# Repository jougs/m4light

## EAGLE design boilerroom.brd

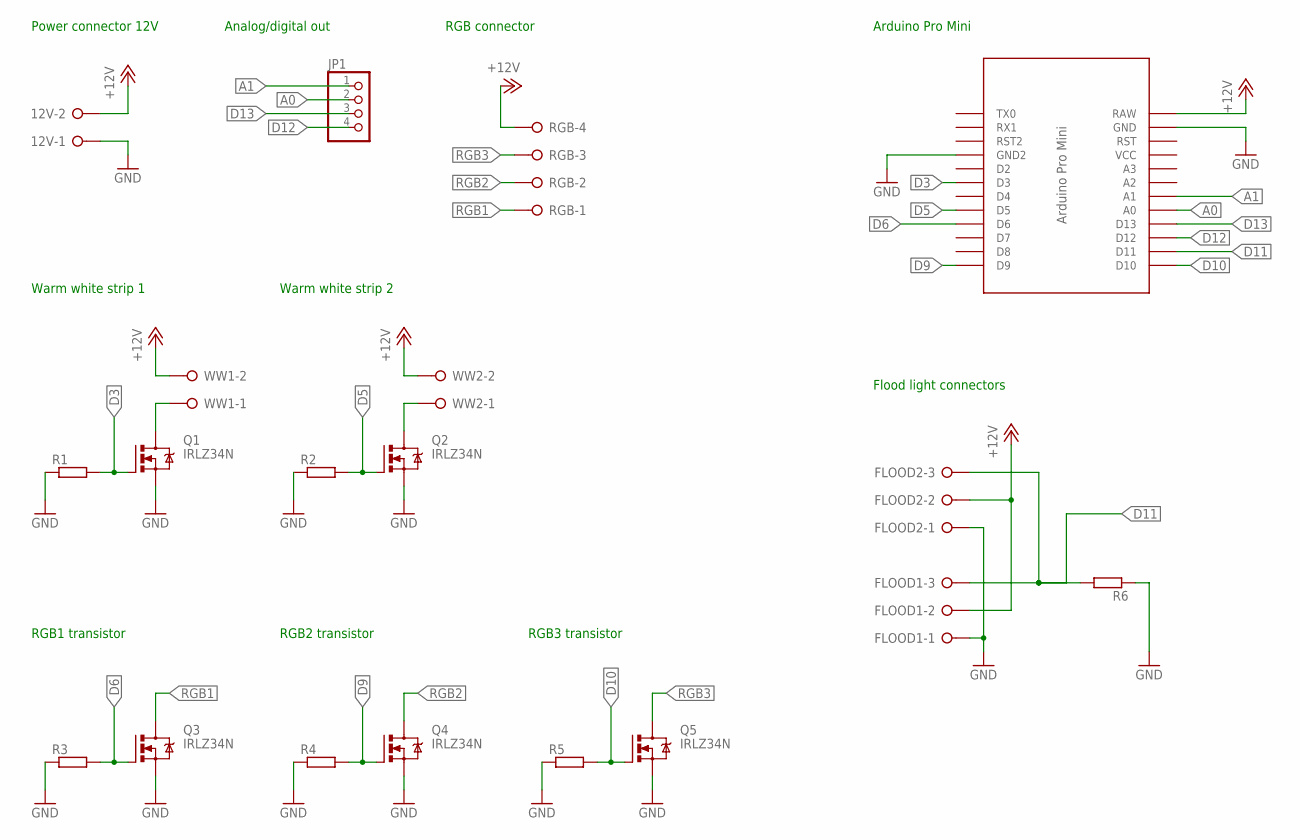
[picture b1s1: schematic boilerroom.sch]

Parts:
12V: W237-02P; W237-132
FLOOD1, FLOOD2: W237-03P; W237-133
JP1: PINHD-1X4; 1X04
Q1, Q2, Q3, Q4, Q5: IRLZ34N; TO220BV
R1, R2, R3, R4, R5, R6: R-EU_0207/10; 0207/10
RGB: W237-04P; W237-4P
U$2: PRO-MINI-3V3
WW1, WW2: W237-02P; W237-132

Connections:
+12V: 12V.2, FLOOD1.2, FLOOD2.2, RGB.4, U$2.RAW, WW1.2, WW2.2
A0: JP1.2, U$2.A0
A1: JP1.1, U$2.A1
D3: Q1.G, R1.2, U$2.D3
D5: Q2.G, R2.2, U$2.D5
D6: Q3.G, R3.2, U$2.D6
D9: Q4.G, R4.2, U$2.D9
D10: Q5.G, R5.2, U$2.D10
D11: FLOOD1.3, FLOOD2.3, R6.2, U$2.D11
D12: JP1.4, U$2.D12
D13: JP1.3, U$2.D13
GND: 12V.1, FLOOD1.1, FLOOD2.1, Q1.S, Q2.S, Q3.S, Q4.S, Q5.S, R1.1, R2.1, R3.1, R4.1, R5.1, R6.1, U$2.GND, U$2.GND1 (GND2)
unnamed: Q2.D, WW2.1
RGB1: Q3.D, RGB.1
RGB2: Q4.D, RGB.2
RGB3: Q5.D, RGB.3
WW1-: Q1.D, WW1.1

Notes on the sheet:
Flood light connectors
Warm white strip 1
Warm white strip 2
Power connector 12V
RGB connector
Analog/digital out
Arduino Pro Mini
RGB1 transistor
RGB2 transistor
RGB3 transistor

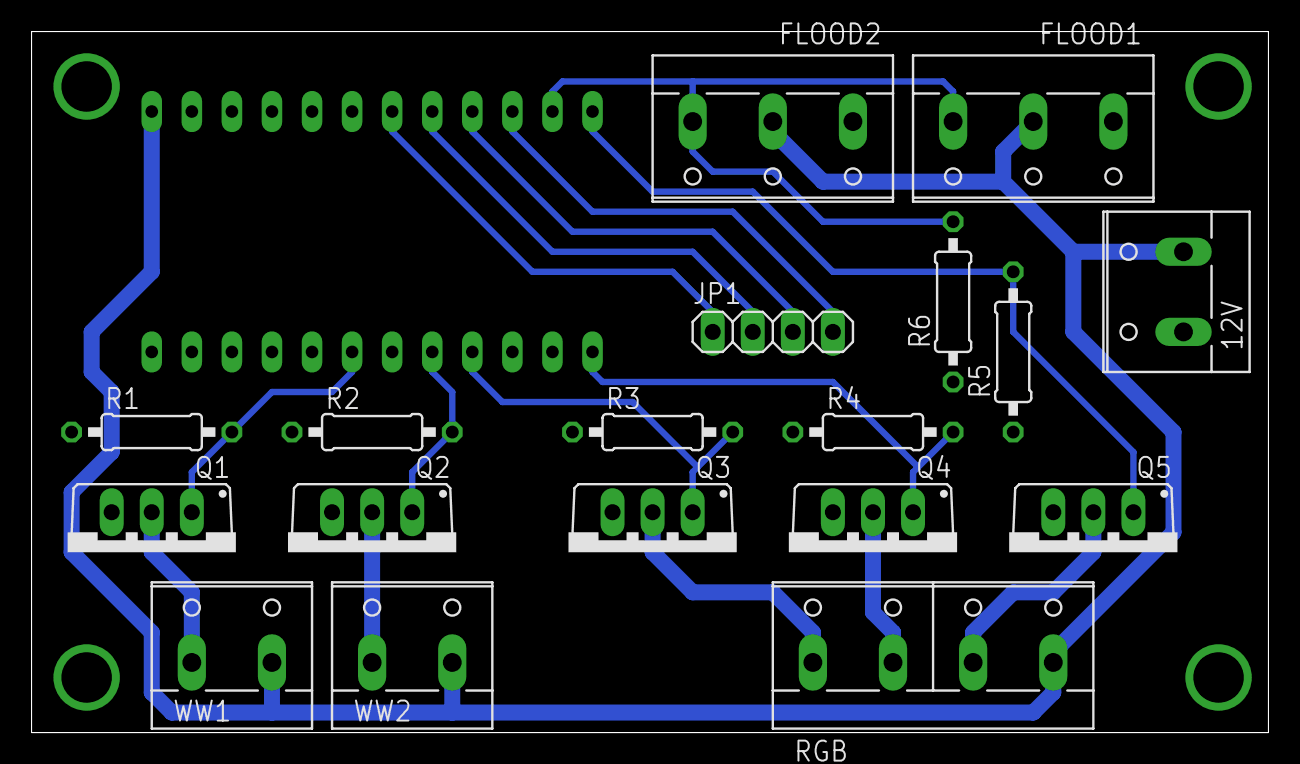
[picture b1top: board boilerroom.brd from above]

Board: 2 copper layers, 78.4 x 44.4 mm, 19 parts (0 on the bottom side), 17 nets.

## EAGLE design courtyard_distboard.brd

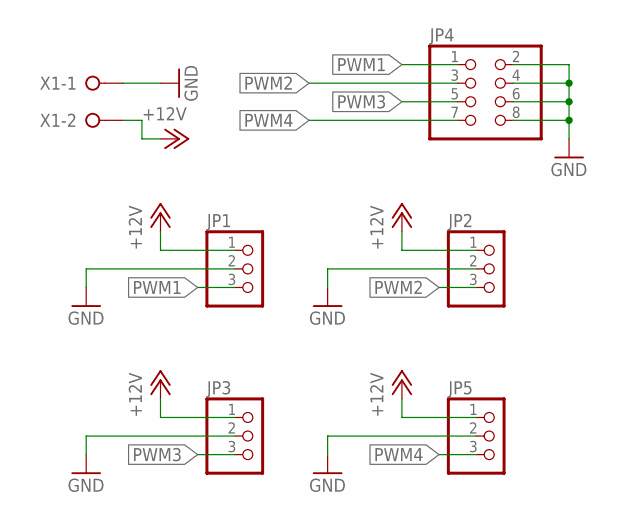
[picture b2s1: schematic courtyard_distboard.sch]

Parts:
JP1, JP2, JP3, JP5: PINHD-1X3; 1X03
JP4: PINHD-2X4; 2X04
X1: W237-02P; W237-132

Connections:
+12V: JP1.1, JP2.1, JP3.1, JP5.1, X1.2
GND: JP1.2, JP2.2, JP3.2, JP4.2, JP4.4, JP4.6, JP4.8, JP5.2, X1.1
PWM1: JP1.3, JP4.1
PWM2: JP2.3, JP4.3
PWM3: JP3.3, JP4.5
PWM4: JP4.7, JP5.3

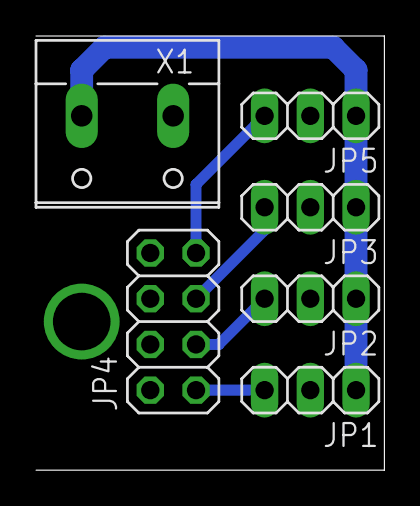
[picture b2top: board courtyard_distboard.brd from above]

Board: 2 copper layers, 19.4 x 24.1 mm, 6 parts (0 on the bottom side), 6 nets.

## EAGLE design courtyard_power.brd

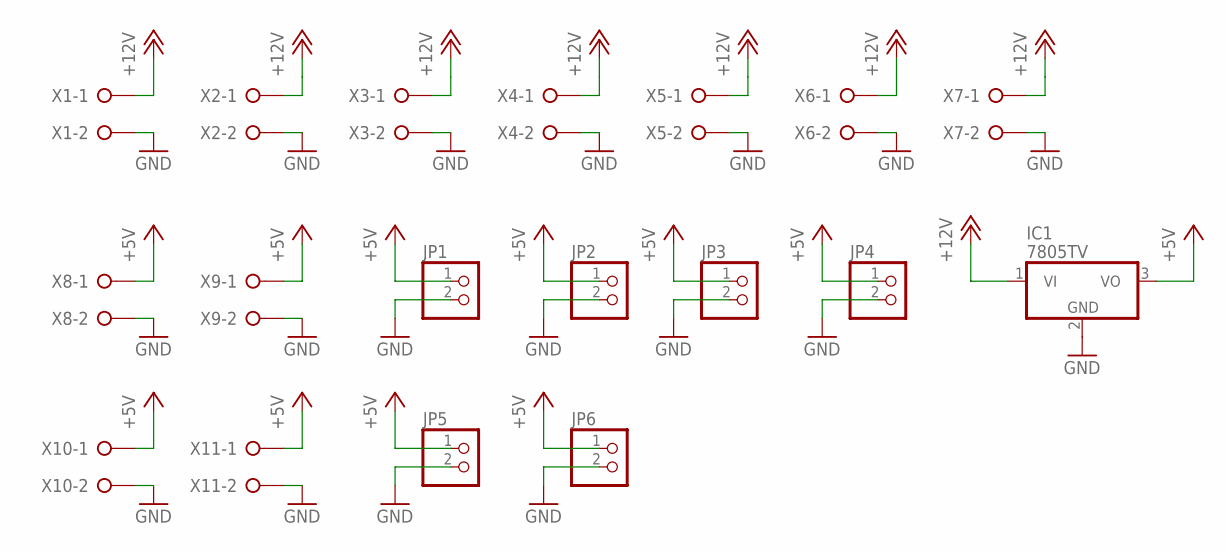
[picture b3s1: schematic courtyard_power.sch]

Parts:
IC1: 7805TV; TO220V
JP1, JP2, JP3, JP4, JP5, JP6: PINHD-1X2; 1X02
X1, X2, X3, X4, X5, X6, X7, X8, X9, X10, X11: W237-02P; W237-132

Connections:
+5V: IC1.3 (VO), JP1.1, JP2.1, JP3.1, JP4.1, JP5.1, JP6.1, X8.1, X9.1, X10.1, X11.1
+12V: IC1.1 (VI), X1.1, X2.1, X3.1, X4.1, X5.1, X6.1, X7.1
GND: IC1.2 (GND), JP1.2, JP2.2, JP3.2, JP4.2, JP5.2, JP6.2, X1.2, X2.2, X3.2, X4.2, X5.2, X6.2, X7.2, X8.2, X9.2, X10.2, X11.2

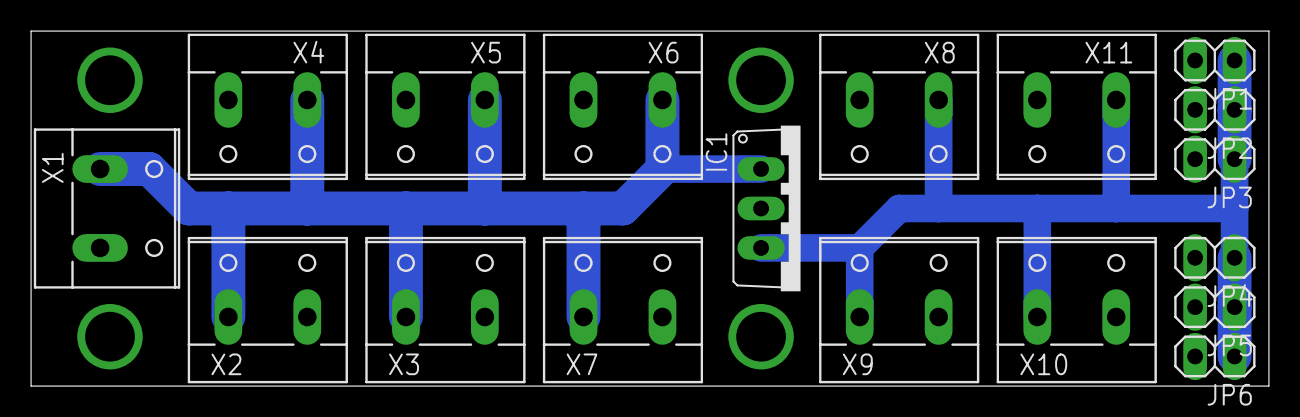
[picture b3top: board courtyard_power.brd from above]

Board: 2 copper layers, 79.7 x 22.9 mm, 18 parts (0 on the bottom side), 3 nets.

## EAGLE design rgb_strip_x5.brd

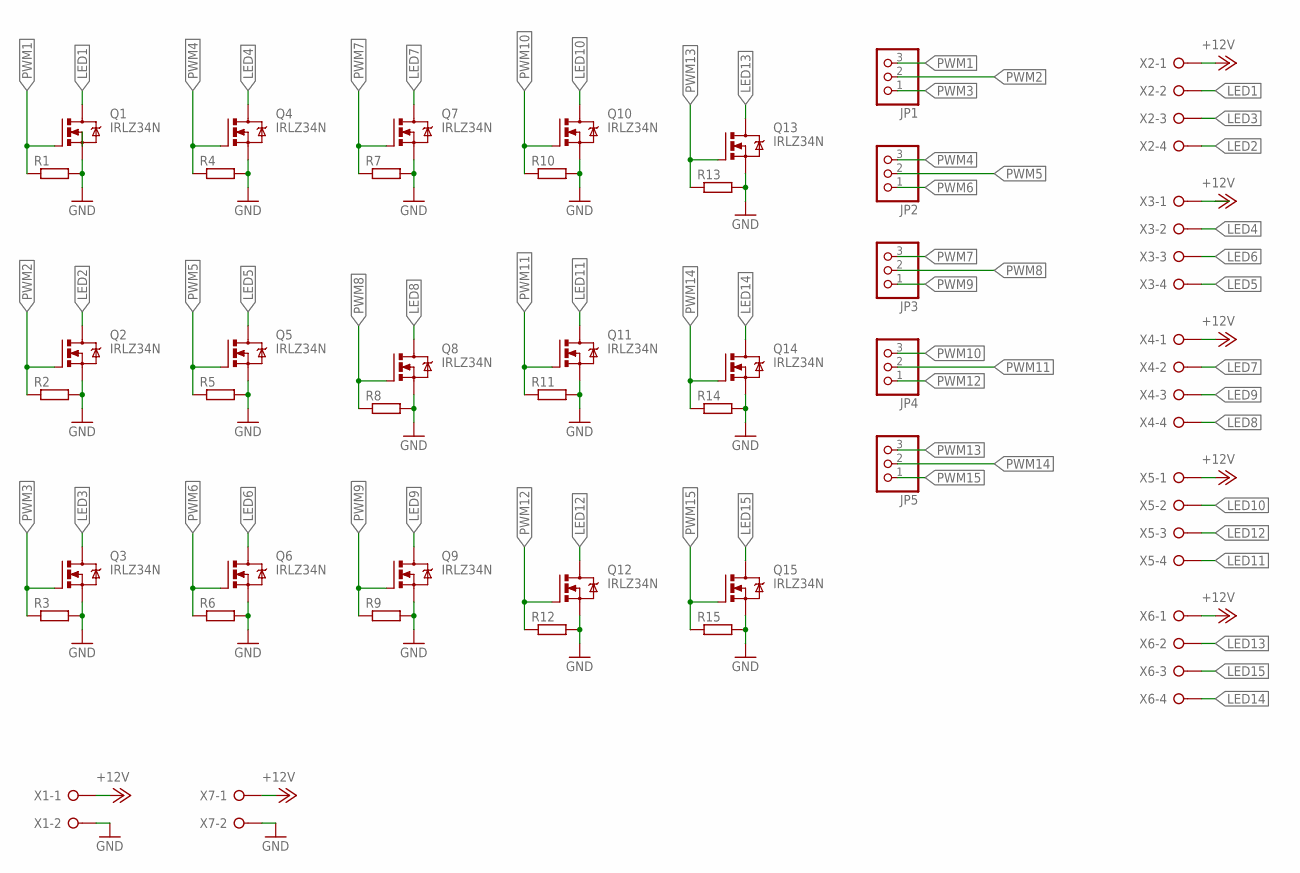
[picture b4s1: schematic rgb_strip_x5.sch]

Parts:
JP1, JP2, JP3, JP4, JP5: PINHD-1X3; 1X03
Q1, Q2, Q3, Q4, Q5, Q6, Q7, Q8, Q9, Q10, Q11, Q12, Q13, Q14, Q15: IRLZ34N; TO220BV
R1, R2, R3, R4, R5, R6, R7, R8, R9, R10, R11, R12, R13, R14, R15: R-EU_0207/10; 0207/10
X1, X7: W237-02P; W237-132
X2, X3, X4, X5, X6: W237-04P; W237-4P

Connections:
+12V: X1.1, X2.1, X3.1, X4.1, X5.1, X6.1, X7.1
GND: Q1.S, Q2.S, Q3.S, Q4.S, Q5.S, Q6.S, Q7.S, Q8.S, Q9.S, Q10.S, Q11.S, Q12.S, Q13.S, Q14.S, Q15.S, R1.2, R2.2, R3.2, R4.2, R5.2, R6.2, R7.2, R8.2, R9.2, R10.2, R11.2, R12.2, R13.2, R14.2, R15.2, X1.2, X7.2
LED1: Q1.D, X2.2
LED2: Q2.D, X2.4
LED3: Q3.D, X2.3
LED4: Q4.D, X3.2
LED5: Q5.D, X3.4
LED6: Q6.D, X3.3
LED7: Q7.D, X4.2
LED8: Q8.D, X4.4
LED9: Q9.D, X4.3
LED10: Q10.D, X5.2
LED11: Q11.D, X5.4
LED12: Q12.D, X5.3
LED13: Q13.D, X6.2
LED14: Q14.D, X6.4
LED15: Q15.D, X6.3
PWM1: JP1.3, Q1.G, R1.1
PWM2: JP1.2, Q2.G, R2.1
PWM3: JP1.1, Q3.G, R3.1
PWM4: JP2.3, Q4.G, R4.1
PWM5: JP2.2, Q5.G, R5.1
PWM6: JP2.1, Q6.G, R6.1
PWM7: JP3.3, Q7.G, R7.1
PWM8: JP3.2, Q8.G, R8.1
PWM9: JP3.1, Q9.G, R9.1
PWM10: JP4.3, Q10.G, R10.1
PWM11: JP4.2, Q11.G, R11.1
PWM12: JP4.1, Q12.G, R12.1
PWM13: JP5.3, Q13.G, R13.1
PWM14: JP5.2, Q14.G, R14.1
PWM15: JP5.1, Q15.G, R15.1

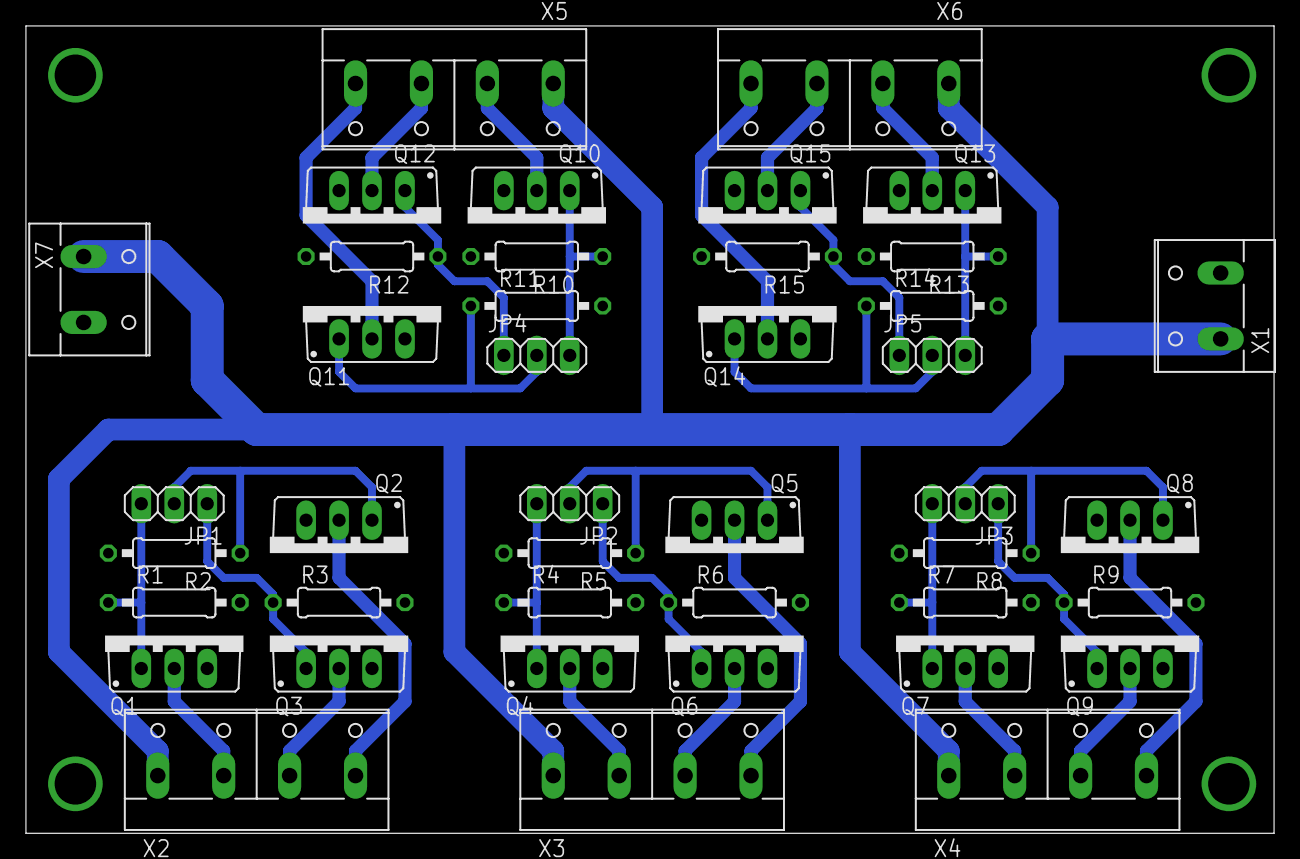
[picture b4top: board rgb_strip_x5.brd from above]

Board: 2 copper layers, 96.2 x 62.2 mm, 42 parts (0 on the bottom side), 32 nets.

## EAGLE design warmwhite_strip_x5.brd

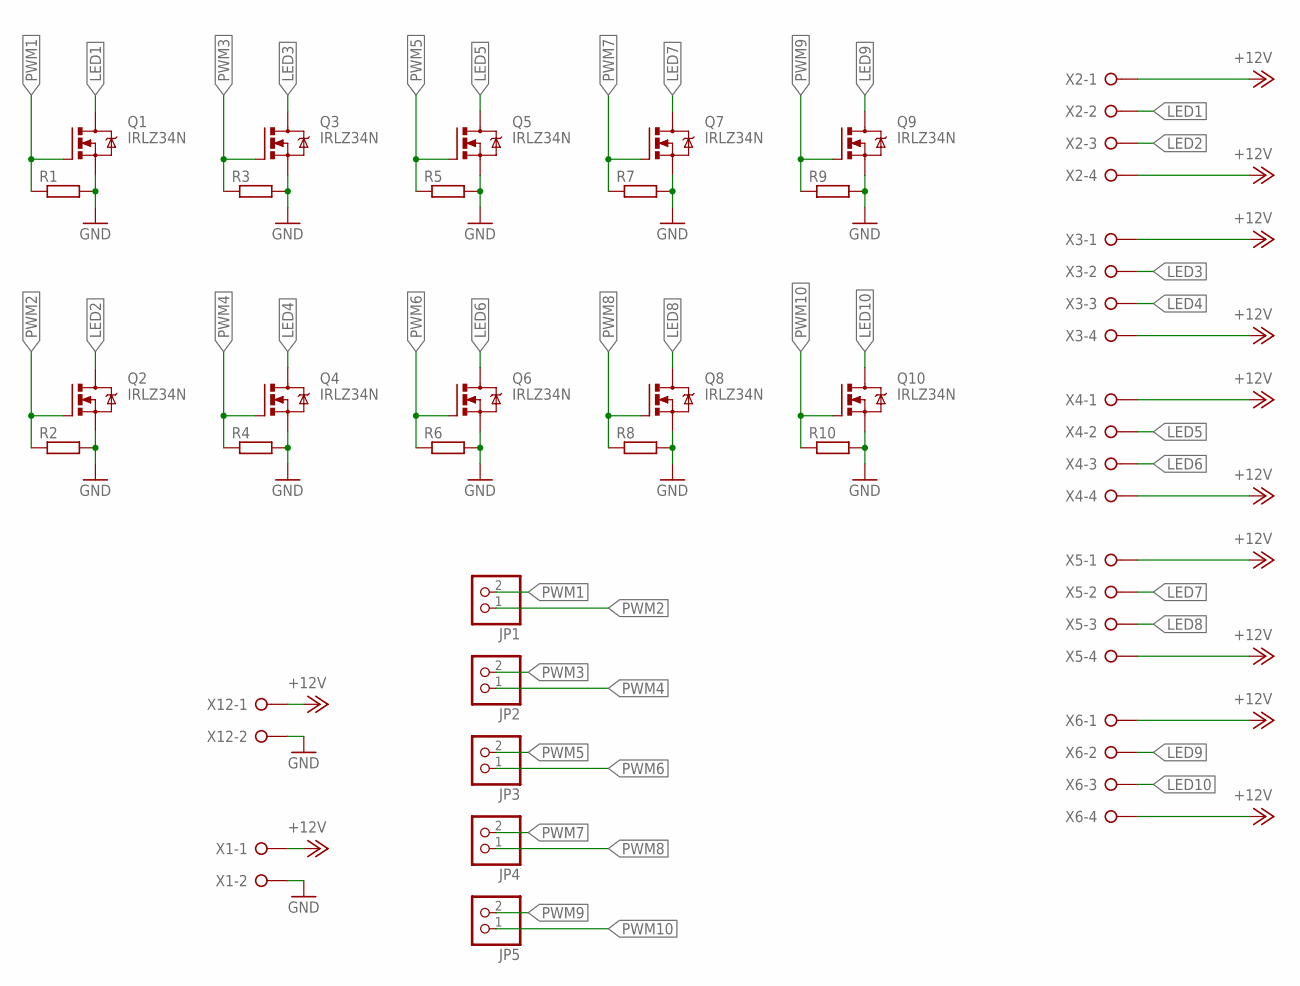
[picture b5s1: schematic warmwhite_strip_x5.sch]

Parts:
JP1, JP2, JP3, JP4, JP5: PINHD-1X2; 1X02
Q1, Q2, Q3, Q4, Q5, Q6, Q7, Q8, Q9, Q10: IRLZ34N; TO220BV
R1, R2, R3, R4, R5, R6, R7, R8, R9, R10: R-EU_0207/10; 0207/10
X1, X12: W237-02P; W237-132
X2, X3, X4, X5, X6: W237-04P; W237-4P

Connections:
+12V: X1.1, X2.1, X2.4, X3.1, X3.4, X4.1, X4.4, X5.1, X5.4, X6.1, X6.4, X12.1
GND: Q1.S, Q2.S, Q3.S, Q4.S, Q5.S, Q6.S, Q7.S, Q8.S, Q9.S, Q10.S, R1.2, R2.2, R3.2, R4.2, R5.2, R6.2, R7.2, R8.2, R9.2, R10.2, X1.2, X12.2
LED1: Q1.D, X2.2
LED2: Q2.D, X2.3
LED3: Q3.D, X3.2
LED4: Q4.D, X3.3
LED5: Q5.D, X4.2
LED6: Q6.D, X4.3
LED7: Q7.D, X5.2
LED8: Q8.D, X5.3
LED9: Q9.D, X6.2
LED10: Q10.D, X6.3
PWM1: JP1.2, Q1.G, R1.1
PWM2: JP1.1, Q2.G, R2.1
PWM3: JP2.2, Q3.G, R3.1
PWM4: JP2.1, Q4.G, R4.1
PWM5: JP3.2, Q5.G, R5.1
PWM6: JP3.1, Q6.G, R6.1
PWM7: JP4.2, Q7.G, R7.1
PWM8: JP4.1, Q8.G, R8.1
PWM9: JP5.2, Q9.G, R9.1
PWM10: JP5.1, Q10.G, R10.1

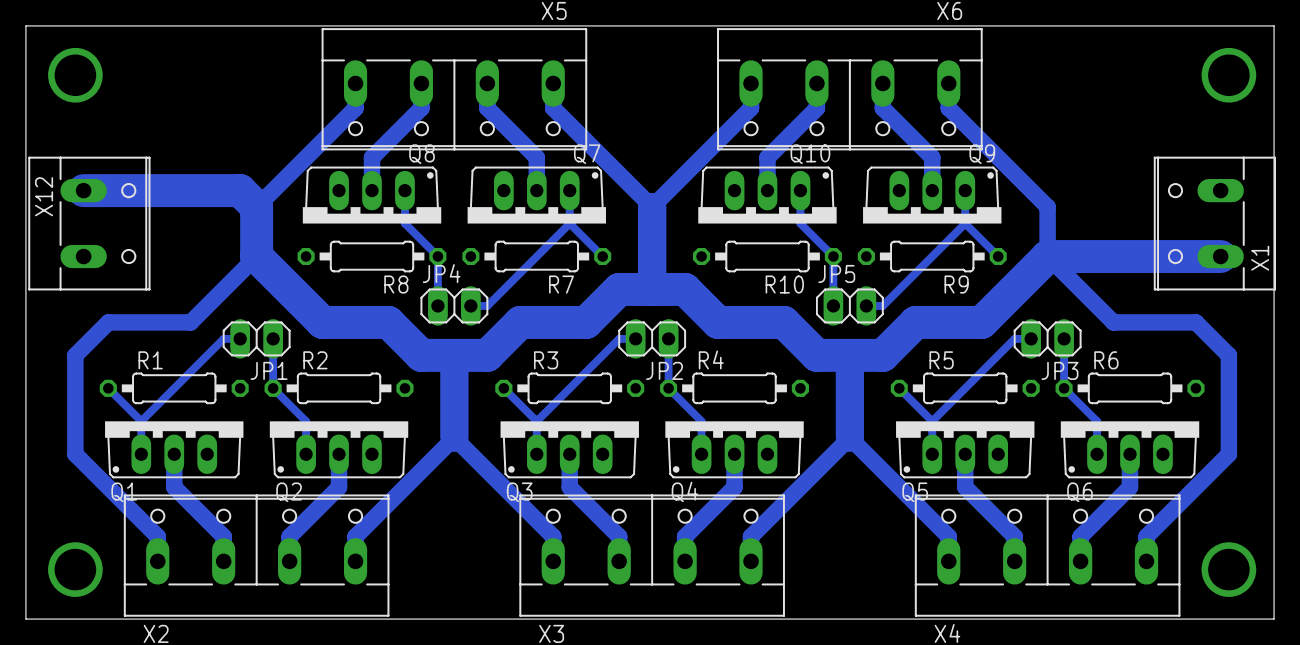
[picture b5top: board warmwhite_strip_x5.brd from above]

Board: 2 copper layers, 96.2 x 45.7 mm, 32 parts (0 on the bottom side), 22 nets.
